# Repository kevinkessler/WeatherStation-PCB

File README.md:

Schematics and PCBs for the ESP32 Based Weather Station using ESP-NOW.

More information can be found [here](https://hackaday.io/project/174898-esp-now-weather-station)

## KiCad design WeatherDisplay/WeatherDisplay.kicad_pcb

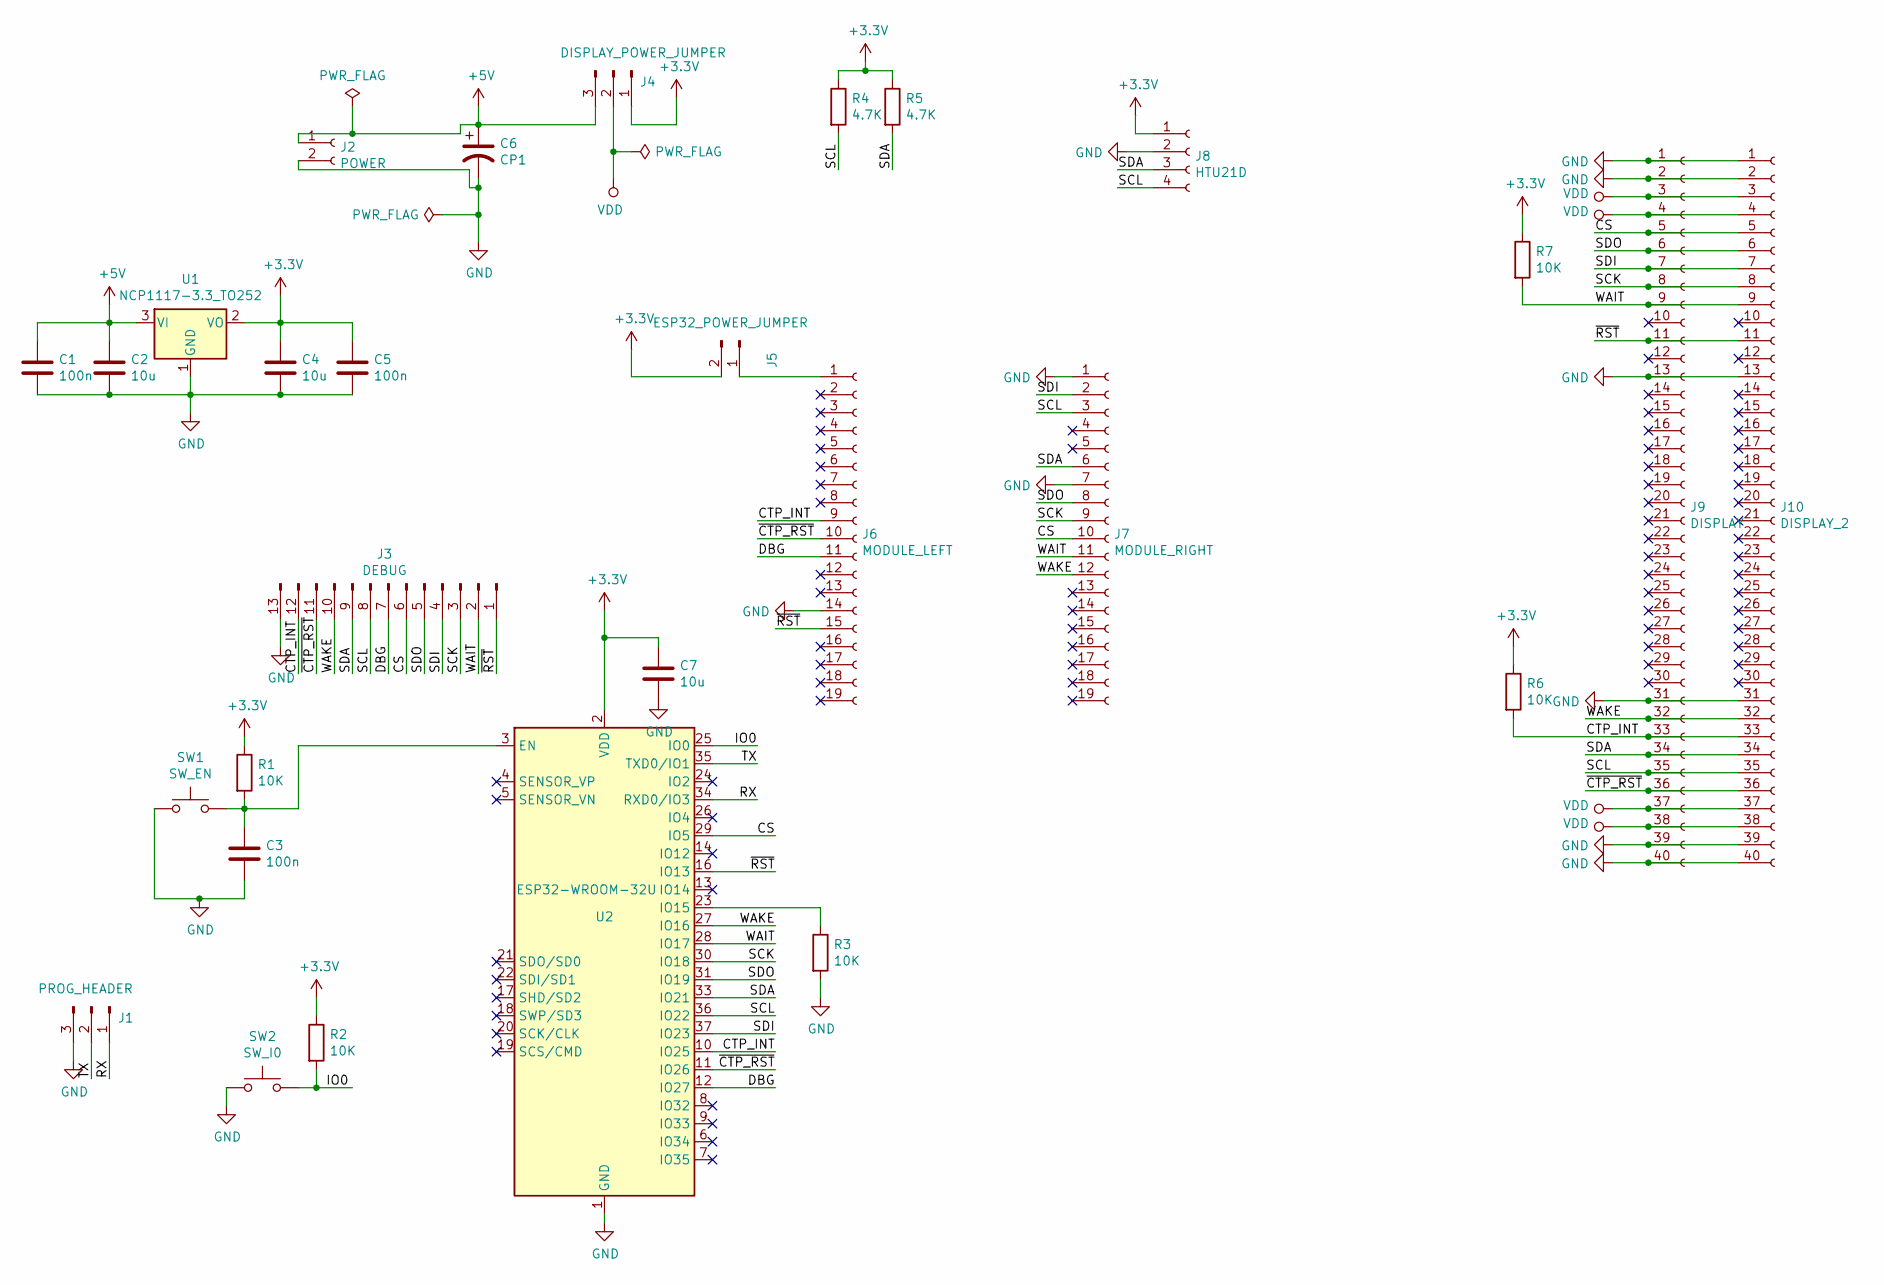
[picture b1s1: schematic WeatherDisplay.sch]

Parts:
C1, C3, C5: 100n; C_0805_2012Metric_Pad1.15x1.40mm_HandSolder
C2, C4, C7: 10u; C_0805_2012Metric_Pad1.15x1.40mm_HandSolder
C6: CP1; CP_Radial_D6.3mm_P2.50mm
J1: PROG_HEADER; PinHeader_1x03_P2.54mm_Vertical
J2: POWER; PinHeader_1x02_P2.54mm_Vertical
J3: DEBUG; PinHeader_1x13_P2.54mm_Vertical
J4: DISPLAY_POWER_JUMPER; PinHeader_1x03_P2.54mm_Vertical
J5: ESP32_POWER_JUMPER; PinHeader_1x02_P2.54mm_Vertical
J6: MODULE_LEFT; PinHeader_1x19_P2.54mm_Vertical
J7: MODULE_RIGHT; PinHeader_1x19_P2.54mm_Vertical
J8: HTU21D; JST_XH_B4B-XH-AM_1x04_P2.50mm_Vertical
J9: DISPLAY; PinHeader_2x20_P2.54mm_Vertical
J10: DISPLAY_2; PinHeader_2x20_P2.54mm_Vertical
R1, R2, R3, R6, R7: 10K; R_0805_2012Metric_Pad1.15x1.40mm_HandSolder
R4, R5: 4.7K; R_0805_2012Metric_Pad1.15x1.40mm_HandSolder
SW1: SW_EN; SW_PUSH_6mm
SW2: SW_I0; SW_PUSH_6mm
U1: NCP1117-3.3_TO252; TO-252-2
U2: ESP32-WROOM-32U

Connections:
+3V3: C4.1, C5.1, C7.1, J4.1, J5.2, J8.1, R1.1, R2.1, R4.1, R5.1, R6.1, R7.1, U1.2 (VO), U2.2 (VDD)
+5V: C1.1, C2.1, C6.1, J2.1, J4.3, U1.3 (VI)
/CS: J3.6, J7.10, J9.5, J10.5, U2.29 (IO5)
/CTP_INT: J3.12, J6.9, J9.33, J10.33, R6.2, U2.10 (IO25)
/DBG: J3.7, J6.11, U2.12 (IO27)
/IO0: R2.2, SW2.2, U2.25 (IO0)
/RX: J1.1, U2.34 (RXD0/IO3)
/SCK: J3.3, J7.9, J9.8, J10.8, U2.30 (IO18)
/SCL: J3.8, J7.3, J8.4, J9.35, J10.35, R4.2, U2.36 (IO22)
/SDA: J3.9, J7.6, J8.3, J9.34, J10.34, R5.2, U2.33 (IO21)
/SDI: J3.4, J7.2, J9.7, J10.7, U2.37 (IO23)
/SDO: J3.5, J7.8, J9.6, J10.6, U2.31 (IO19)
/TX: J1.2, U2.35 (TXD0/IO1)
/WAIT: J3.2, J7.11, J9.9, J10.9, R7.2, U2.28 (IO17)
/WAKE: J3.10, J7.12, J9.32, J10.32, U2.27 (IO16)
/~CTP_RST: J3.11, J6.10, J9.36, J10.36, U2.11 (IO26)
/~RST: J3.1, J6.15, J9.11, J10.11, U2.16 (IO13)
GND: C1.2, C2.2, C3.2, C4.2, C5.2, C6.2, C7.2, J1.3, J2.2, J3.13, J6.14, J7.1, J7.7, J8.2, J9.1, J9.2, J9.13, J9.31, J9.39, J9.40, J10.1, J10.2, J10.13, J10.31, J10.39, J10.40, R3.2, SW1.1, SW2.1, U1.1 (GND), U2.1 (GND), U2.15 (GND), U2.38 (GND), U2.39 (GND)
unnamed: C3.1, R1.2, SW1.2, U2.3 (EN)
unnamed: J5.1, J6.1
unnamed: R3.1, U2.23 (IO15)
VDD: J4.2, J9.3, J9.4, J9.37, J9.38, J10.3, J10.4, J10.37, J10.38

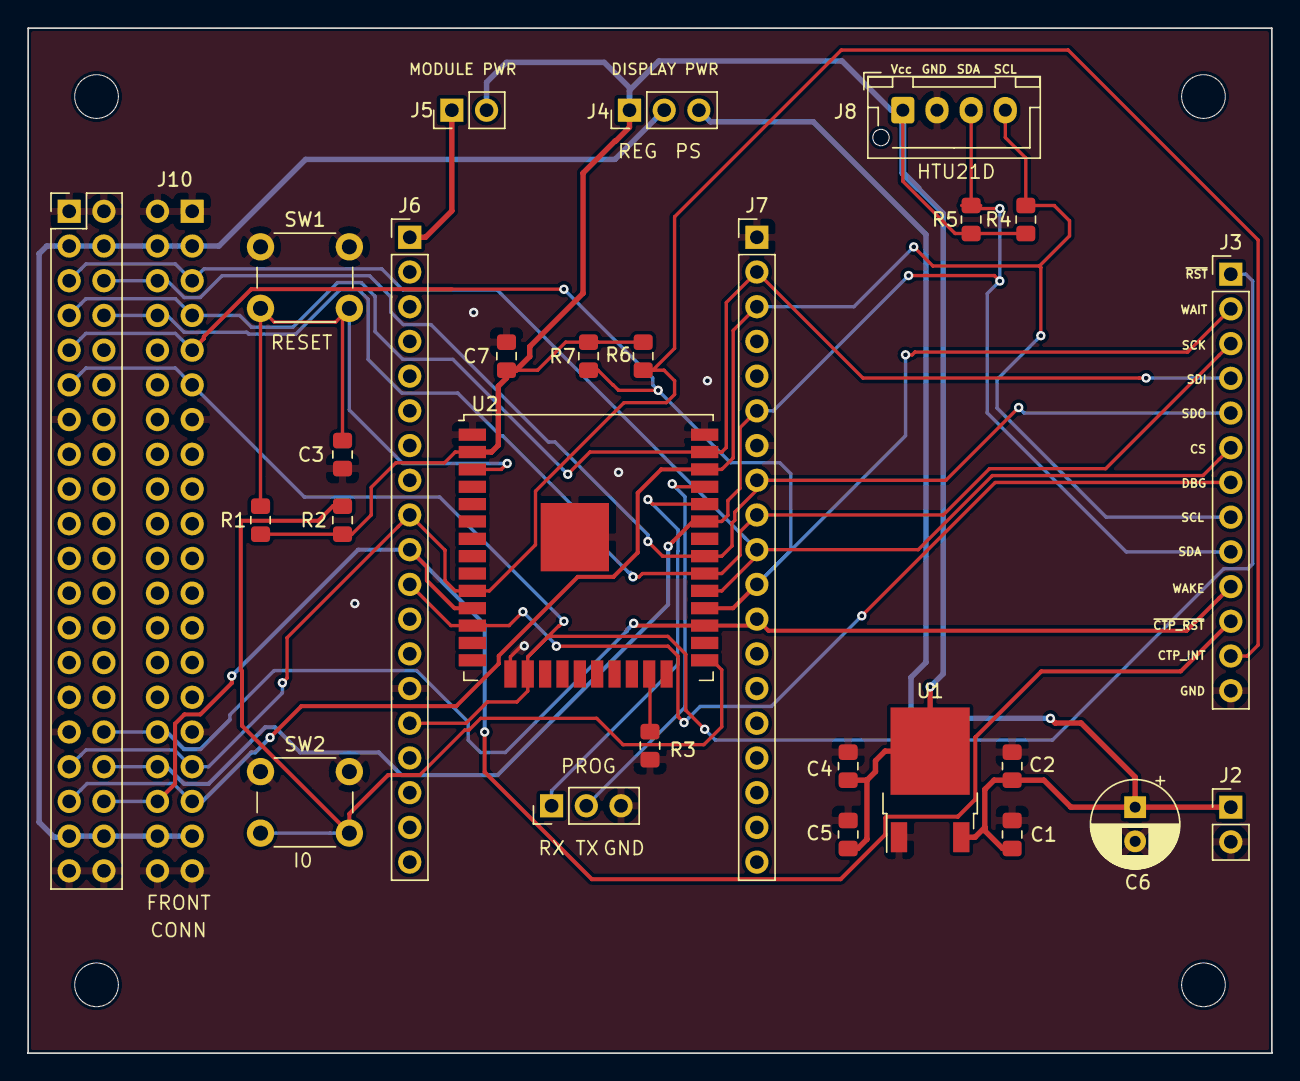
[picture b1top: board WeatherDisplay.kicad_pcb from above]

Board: 2 copper layers, 91.0 x 75.0 mm, 28 parts (1 on the bottom side), 22 nets.

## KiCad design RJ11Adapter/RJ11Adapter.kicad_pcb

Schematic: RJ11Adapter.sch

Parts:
J1: RAIN_GAUGE; A-2014-1-4-N-T-R
J2: WIND_RAIN; JST_PH_B6B-PH-SM4-TB_1x06-1MP_P2.00mm_Vertical
J3: WIND; A-2014-1-4-N-T-R

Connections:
/ANEM_A: J2.3, J3.3
/ANEM_B: J2.4, J3.4
/RAIN_A: J1.3, J2.1
/RAIN_B: J1.4, J2.6
/VANE_A: J2.2, J3.2
/VANE_B: J2.5, J3.5

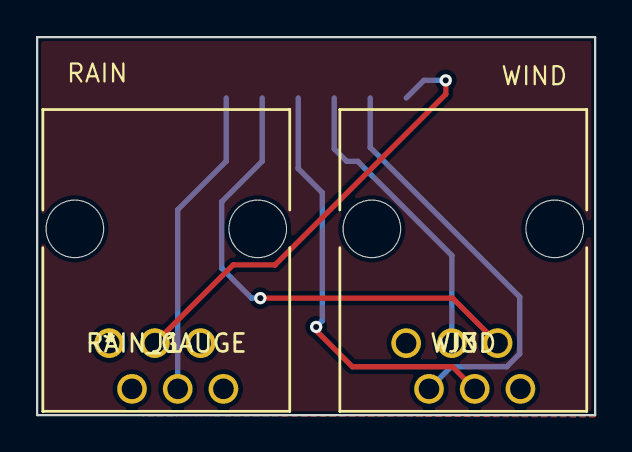
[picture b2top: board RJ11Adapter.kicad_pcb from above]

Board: 2 copper layers, 31.0 x 21.0 mm, 3 parts (1 on the bottom side), 6 nets.

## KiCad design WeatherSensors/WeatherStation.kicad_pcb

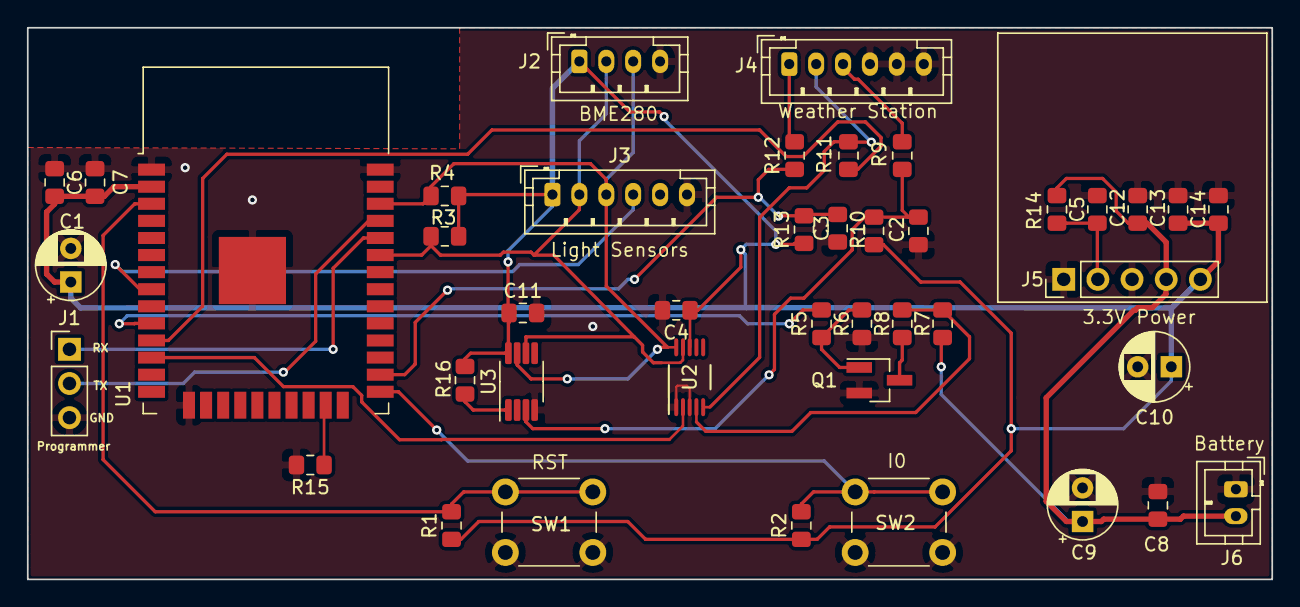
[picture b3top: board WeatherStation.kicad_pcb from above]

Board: 2 copper layers, 92.5 x 41.0 mm, 42 parts (0 on the bottom side), 24 nets.

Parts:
C1, C9, C10: 100u; CP_Radial_D5.0mm_P2.50mm
C2, C3: 10p; C_0805_2012Metric_Pad1.15x1.40mm_HandSolder
C4, C5, C6, C8, C11: 100n; C_0805_2012Metric_Pad1.15x1.40mm_HandSolder
C7: 10n; C_0805_2012Metric_Pad1.15x1.40mm_HandSolder
C12, C13, C14: 10u; C_0805_2012Metric_Pad1.15x1.40mm_HandSolder
J1: PROG_HEADER; PinHeader_1x03_P2.54mm_Vertical
J2: I2C_PORT; JST_PH_B4B-PH-K_1x04_P2.00mm_Vertical
J3: LIGHT_HEADER; JST_PH_B6B-PH-K_1x06_P2.00mm_Vertical
J4: WIND_RAIN; JST_PH_B6B-PH-K_1x06_P2.00mm_Vertical
J5: PWR_HEADER; PinHeader_1x05_P2.54mm_Vertical
J6: BATTERY_HEADER; JST_PH_B2B-PH-K_1x02_P2.00mm_Vertical
Q1: Q_NMOS_GSD; SOT-23_Handsoldering
R1, R2, R7, R8, R14, R15, R16: 1K; R_0805_2012Metric_Pad1.15x1.40mm_HandSolder
R3, R4: 4.7K; R_0805_2012Metric_Pad1.15x1.40mm_HandSolder
R5, R9, R12: 100; R_0805_2012Metric_Pad1.15x1.40mm_HandSolder
R6: 100K; R_0805_2012Metric_Pad1.15x1.40mm_HandSolder
R10, R13: 330K; R_0805_2012Metric_Pad1.15x1.40mm_HandSolder
R11: 10K; R_0805_2012Metric_Pad1.15x1.40mm_HandSolder
SW1: SW_EN; SW_PUSH_6mm
SW2: SW_I00; SW_PUSH_6mm
U1: ESP32-WROOM-32D; ESP32-WROOM-32
U2: ADS1115IDGSR
U3: S35770; MSOP-8_3x3mm_P0.65mm

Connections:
+3V3: C1.1, C4.1, C6.1, C7.1, C10.1, C11.1, C13.1, C14.1, J2.1, J3.1, J5.5, R1.1, R2.1, R3.1, R4.1, R10.1, R13.1, R16.1, U1.2, U2.8, U3.8
+BATT: C8.1, C9.1, C12.1, J5.4, J6.2, R7.1, R14.1
/ADC0: R7.2, R8.1, U2.4
/ADC1: J4.2, R11.1, U2.5
/ADC_ALERT: U1.12, U2.2
/ANEM_PIN: C2.1, R9.1, R10.2, U3.3
/ANEM_SWITCH: J4.3, R9.2
/PWR_PIN_GND: R5.2, U1.10
/RAIN_PIN: C3.1, R12.1, R13.2, U1.26
/RAIN_SWITCH: J4.1, R12.2
/SCL: J2.3, J3.3, R4.2, U1.36, U2.10, U3.7
/SDA: J2.2, J3.2, R3.2, U1.33, U2.9, U3.6
/SI_INT: J3.4, U1.8
/WIND_VCC: R11.2, U1.11
GND: C1.2, C2.2, C3.2, C4.2, C5.2, C6.2, C7.2, C8.2, C9.2, C10.2, C11.2, C12.2, C13.2, C14.2, J1.3, J2.4, J3.6, J4.4, J4.5, J4.6, J5.1, J5.3, J6.1, Q1.2, R6.2, R15.2, SW1.1, SW2.1, U1.1, U1.15, U1.38, U1.39, U2.1, U2.3, U3.4
unnamed: C5.1, J5.2, R14.2
unnamed: J1.1, U1.34
unnamed: J1.2, U1.35
unnamed: Q1.1, R5.1, R6.1
unnamed: Q1.3, R8.2
unnamed: R1.2, SW1.2, U1.3
unnamed: R2.2, SW2.2, U1.25
unnamed: R15.1, U1.23
unnamed: R16.2, U3.1

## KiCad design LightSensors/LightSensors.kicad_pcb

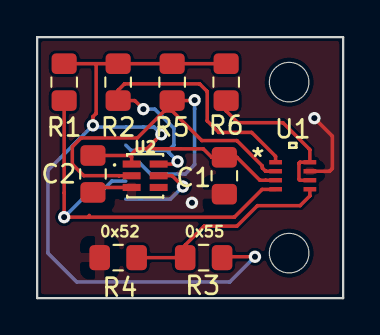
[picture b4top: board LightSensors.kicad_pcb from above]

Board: 2 copper layers, 17.0 x 14.5 mm, 11 parts (1 on the bottom side), 8 nets.

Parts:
C1, C2: 100n; C_0805_2012Metric_Pad1.15x1.40mm_HandSolder
J1: Conn_01x06_Male; JST_SH_BM06B-SRSS-TB_1x06-1MP_P1.00mm_Vertical
R1, R2, R5: 4.7K; R_0805_2012Metric_Pad1.15x1.40mm_HandSolder
R3, R4: 0; R_0805_2012Metric_Pad1.15x1.40mm_HandSolder
R6: 10K; R_0805_2012Metric_Pad1.15x1.40mm_HandSolder
U1: 10QFN_2X2_SIL; SI1133-AA00-GMR
U2: TCS34725FN; SON65P200X240X70-6N

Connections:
+3V3: C1.1, C2.1, J1.1, R1.1, R2.1, R3.1, R5.1, R6.1, U1.3, U2.1
/SCL: J1.3, R5.2, U1.2, U2.2
/SDA: J1.2, R2.2, U1.1, U2.6
/SI_INT: J1.4, R1.2, U1.4
/TCS_INT: J1.5, U2.5
GND: C1.2, C2.2, J1.6, R4.2, U1.8, U2.3
unnamed: R3.2, R4.1, U1.6
unnamed: R6.2, U1.7, U1.9

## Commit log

2020-09-27 RJ11 Adapter
2020-09-27 gitignore
2020-09-29 Light Sensors
2020-10-12 New A-2014-1-4-N-T-R Footprint
2021-04-14 East Rising Display PCB
2021-04-15 Test SSH Key

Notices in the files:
parts and their libraries:
Copyright 2016 Accelerated Designs. All rights reserved.
